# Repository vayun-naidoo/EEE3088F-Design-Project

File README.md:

**EEE3088F MICRO MOUSE DESIGN PROJECT**  
The project requires the construction of two submodules that interface with a micromouse robot. The robot is designed to complete a maze after finding the most optimal path to traverse.
The two submodules are for the **power** and **sensing** requirements of the micromouse. All design schematics and datasheets considered can be found in this repository.  

**POWER**  
The power submodule is required to distrubute the power from a 1S1P battery to the motors on the micromouse as well as power the other submodules such as the processor and the sensing apparatus. 
THe system is also required to monitor the battery's state of charge (SoC) through the processor's ADC.

**SENSING**  
The sensing subsystem is required to, at close range(+-5cm) produce a voltage to the micro controller. This voltage must be distinguishable from a further range output(+10cm). It is also required to not drain the battery of the micro mouse as it needs to traverse a maze for roughly 10 minutes.

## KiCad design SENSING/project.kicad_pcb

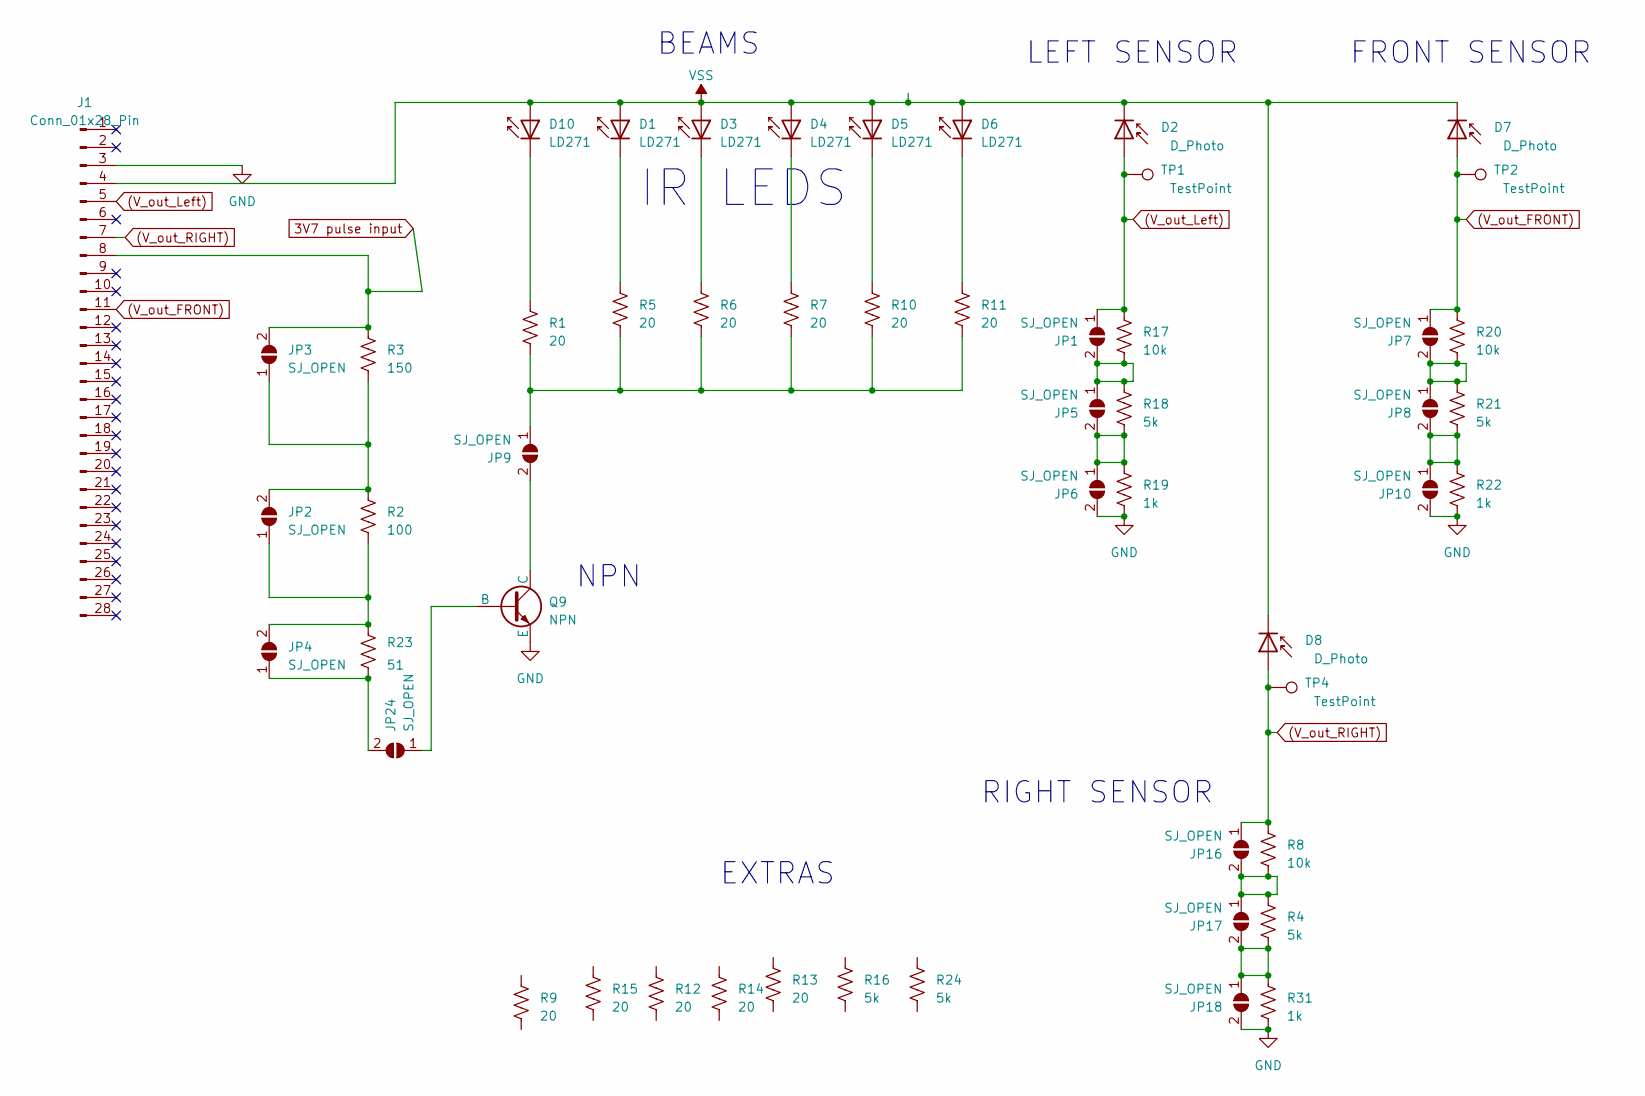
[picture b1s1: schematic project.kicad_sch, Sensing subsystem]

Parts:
D1, D3, D4, D5, D6, D10: LD271; LED_SideEmitter_Rectangular_W4.5mm_H1.6mm; LCSC C57092
D2, D7, D8: D_Photo; LED_D5.0mm_Horizontal_O1.27mm_Z3.0mm_IRBlack; LCSC C2900211
J1: Conn_01x28_Pin; PinSocket_2x14_P2.54mm_Vertical
JP1, JP2, JP3, JP4, JP5, JP6, JP7, JP8, JP9, JP10, JP16, JP17, JP18, JP24: SJ_OPEN; SolderJumper-2_P1.3mm_Open_RoundedPad1.0x1.5mm
Q9: NPN; SOT-23; LCSC C139719
R1, R5, R6, R7, R9, R10, R11, R12, R13, R14, R15: 20; R_0805_2012Metric; LCSC C17544
R2: 100; R_0805_2012Metric; LCSC C17408
R3: 150; R_0805_2012Metric; LCSC C17471
R4, R16, R18, R21, R24: 5k; R_0805_2012Metric; LCSC C27834
R8, R17, R20: 10k; R_0805_2012Metric; LCSC C17414
R19, R22, R31: 1k; R_0805_2012Metric; LCSC C17513
R23: 51; R_0805_2012Metric; LCSC C17738
TP1, TP2, TP4: TestPoint; TestPoint_Pad_1.5x1.5mm

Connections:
3V7 pulse input: J1.8, JP3.2 (B), R3.2
(V_out_FRONT): D7.2 (A), J1.11, JP7.1 (A), R20.1, TP2.1
(V_out_Left): D2.2 (A), J1.5, JP1.1 (A), R17.1, TP1.1
(V_out_RIGHT): D8.2 (A), J1.7, JP16.1 (A), R8.1, TP4.1
GND: J1.3, JP6.2 (B), JP10.2 (B), JP18.2 (B), Q9.3 (E), R19.2, R22.2, R31.2
unnamed: D1.1 (K), R5.2
unnamed: D3.1 (K), R6.2
unnamed: D4.1 (K), R7.2
unnamed: D5.1 (K), R10.2
unnamed: D6.1 (K), R11.2
unnamed: D10.1 (K), R1.2
unnamed: JP1.2 (B), JP5.1 (A), R17.2, R18.1
unnamed: JP2.1 (A), JP4.2 (B), R2.1, R23.2
unnamed: JP2.2 (B), JP3.1 (A), R2.2, R3.1
unnamed: JP5.2 (B), JP6.1 (A), R18.2, R19.1
unnamed: JP7.2 (B), JP8.1 (A), R20.2, R21.1
unnamed: JP9.1 (A), R1.1, R5.1, R6.1, R7.1, R10.1, R11.1
unnamed: JP9.2 (B), Q9.1 (C)
unnamed: JP8.2 (B), JP10.1 (A), R21.2, R22.1
unnamed: JP16.2 (B), JP17.1 (A), R4.1, R8.2
unnamed: JP17.2 (B), JP18.1 (A), R4.2, R31.1
unnamed: JP24.1 (A), Q9.2 (B)
unnamed: JP4.1 (A), JP24.2 (B), R23.1
VSS: D1.2 (A), D2.1 (K), D3.2 (A), D4.2 (A), D5.2 (A), D6.2 (A), D7.1 (K), D8.1 (K), D10.2 (A), J1.4

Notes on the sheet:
NPN
LEFT SENSOR
IR LEDS
EXTRAS
FRONT SENSOR
BEAMS
RIGHT SENSOR

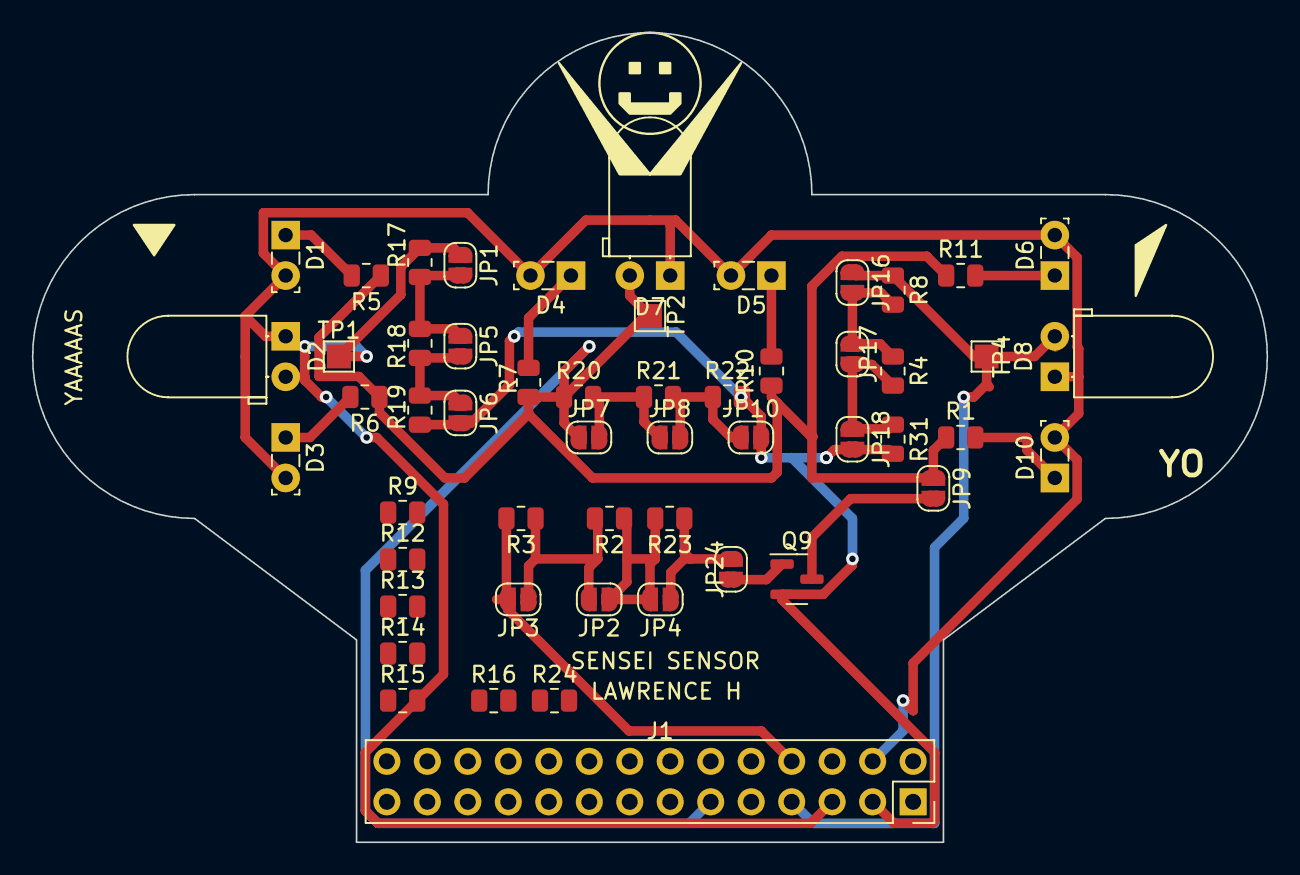
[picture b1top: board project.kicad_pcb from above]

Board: 2 copper layers, 77.5 x 50.8 mm, 53 parts (0 on the bottom side), 24 nets.

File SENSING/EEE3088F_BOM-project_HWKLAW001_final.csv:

Comment,Designator,Footprint,LCSC
NPN,Q9,SOT-23,C139719
100,R2,R_0805_2012Metric,C17408
10k,"R17,R20,R8",R_0805_2012Metric,C17414
150,R3,R_0805_2012Metric,C17471
1k,"R19,R22,R31",R_0805_2012Metric,C17513
20,"R1,R10,R11,R12,R13,R14,R15,R5,R6,R7,R9",R_0805_2012Metric,C17544
51,R23,R_0805_2012Metric,C17738
5k,"R16,R18,R21,R24,R4",R_0805_2012Metric,C27834
D_Photo,"D2,D7,D8",LED_D5.0mm_Horizontal_O1.27mm_Z3.0mm_IRBlack,C2900211
LD271,"D1,D10,D3,D4,D5,D6",LED_SideEmitter_Rectangular_W4.5mm_H1.6mm,C57092
SJ_OPEN,JP17,SolderJumper-2_P1.3mm_Open_RoundedPad1.0x1.5mm,
SJ_OPEN,JP2,SolderJumper-2_P1.3mm_Open_RoundedPad1.0x1.5mm,
SJ_OPEN,JP5,SolderJumper-2_P1.3mm_Open_RoundedPad1.0x1.5mm,
SJ_OPEN,JP10,SolderJumper-2_P1.3mm_Open_RoundedPad1.0x1.5mm,
SJ_OPEN,JP6,SolderJumper-2_P1.3mm_Open_RoundedPad1.0x1.5mm,
SJ_OPEN,JP7,SolderJumper-2_P1.3mm_Open_RoundedPad1.0x1.5mm,
TestPoint,TP1,TestPoint_Pad_1.5x1.5mm,
TestPoint,TP4,TestPoint_Pad_1.5x1.5mm,
SJ_OPEN,JP16,SolderJumper-2_P1.3mm_Open_RoundedPad1.0x1.5mm,
SJ_OPEN,JP8,SolderJumper-2_P1.3mm_Open_RoundedPad1.0x1.5mm,
SJ_OPEN,JP9,SolderJumper-2_P1.3mm_Open_RoundedPad1.0x1.5mm,
Conn_01x28_Pin,J1,PinSocket_2x14_P2.54mm_Vertical,
SJ_OPEN,JP3,SolderJumper-2_P1.3mm_Open_RoundedPad1.0x1.5mm,
SJ_OPEN,JP24,SolderJumper-2_P1.3mm_Open_RoundedPad1.0x1.5mm,
SJ_OPEN,JP4,SolderJumper-2_P1.3mm_Open_RoundedPad1.0x1.5mm,
SJ_OPEN,JP1,SolderJumper-2_P1.3mm_Open_RoundedPad1.0x1.5mm,
SJ_OPEN,JP18,SolderJumper-2_P1.3mm_Open_RoundedPad1.0x1.5mm,
TestPoint,TP2,TestPoint_Pad_1.5x1.5mm,

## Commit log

2024-03-16 Create blahblah
2024-03-16 Rename ANDLV8548MC-D.pdf to POWER/ANDLV8548MC-D.pdf
2024-03-16 Rename drv8837.pdf to POWER/drv8837.pdf
2024-03-16 Create sensing stuff
2024-03-24 Add files via upload
    final design submitted
2024-04-19 Sensing Update README.md
2024-04-19 README.md
